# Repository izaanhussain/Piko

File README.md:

# Piko
My cute mini cute keychain with ESP32-C3 SuperMini , 0.96-inch SSD1306 OLED , TTP223 touch , six indicator LEDs and a active buzzer.
the repo has a custom KiCad PCB, Gerber files and a basic Arduino animation firmware that displays the bitmapped frames of the 712 GIFs with touch and led controls.

# Details
1) ESP32-C3 SuperMini as the controller
2) 0.96-inch, 128×64 SSD1306 I²C OLED
3) Bitmap-frame animation at a target of approximately 24 FPS
4) TTP223 touch sensor input
5) Buzzer connection
6) 6 leds & 6 resitors
7) 1 transistor
8) LiPo battery connection pads
9) Custom PCB designed in KiCad
10) KiCad source files and Gerber files included

## Required Library Setup

Open Arduino IDE
Install OLED libraries: Tools -> Manage Libraries -> search Adafruit SSD1306 -> install
fig1

Add esp32 additional board manager URL: Files -> Preferences -> add https://raw.githubusercontent.com/espressif/arduino-esp32/gh-pages/package_esp32_dev_index.json to Additional Boards Manager URLs

install esp32 board manager: Tools -> Board -> Boards Manager -> search esp32 -> install esp32 by Espressif Systems

## Components 
 refer BOM.csv

## ## Display

The project uses a:

**0.96" 128×64 SSD1306 I2C OLED**

The OLED is connected directly to the ESP32-C3.

## Pin connections

The firmware uses the I²C pins given below on the ESP32-C3 SuperMini:-

| Signal | ESP32-C3 pin |
|---|---|
| OLED SDA | GPIO8 |
| OLED SCL | GPIO9 |
| OLED power | 3V3 |
| OLED ground | GND |
| TTP223 output | GPIO3 |

## 
## Firmware

The Arduino firmware and bitmap frames are provided in `Firmware' folder

## Firmware Installation 

1. Download the raw PIKO_FIRMWARE.zip file
2. open Arduino IDE
3. open PIKO_FIRMWARE.ino
4. upload to your device

### Requirements for uploading firmware

1) Arduino IDE
2) ESP32 Arduino core
3) **Adafruit GFX Library**
4) **Adafruit SSD1306**

### Upload

1. extract Firmware/PIKO_FIRMWARE.zip
2. open the PIKO_FIRMWARE.ino file
3. ensure that all_frames.h is in the same directory as the sketch
4. install the Adafruit GFX and Adafruit SSD1306 libraries using Library Manager
5. select the correct ESP32-C3 board and serial port
6. upload the sketch and open the Serial Monitor (with baud rate 115200)

The current firmware targets 42 ms per frame (means about 24 FPS).

## PCB 

## SHEMATICS

## CREDITS 
 CREDITS TO MYSELF EVERYTHINGG OWN IDEA HEHE and THIS PROJECT WAS MADE FOR #EMBASSY YSWS BY HACKCLUB

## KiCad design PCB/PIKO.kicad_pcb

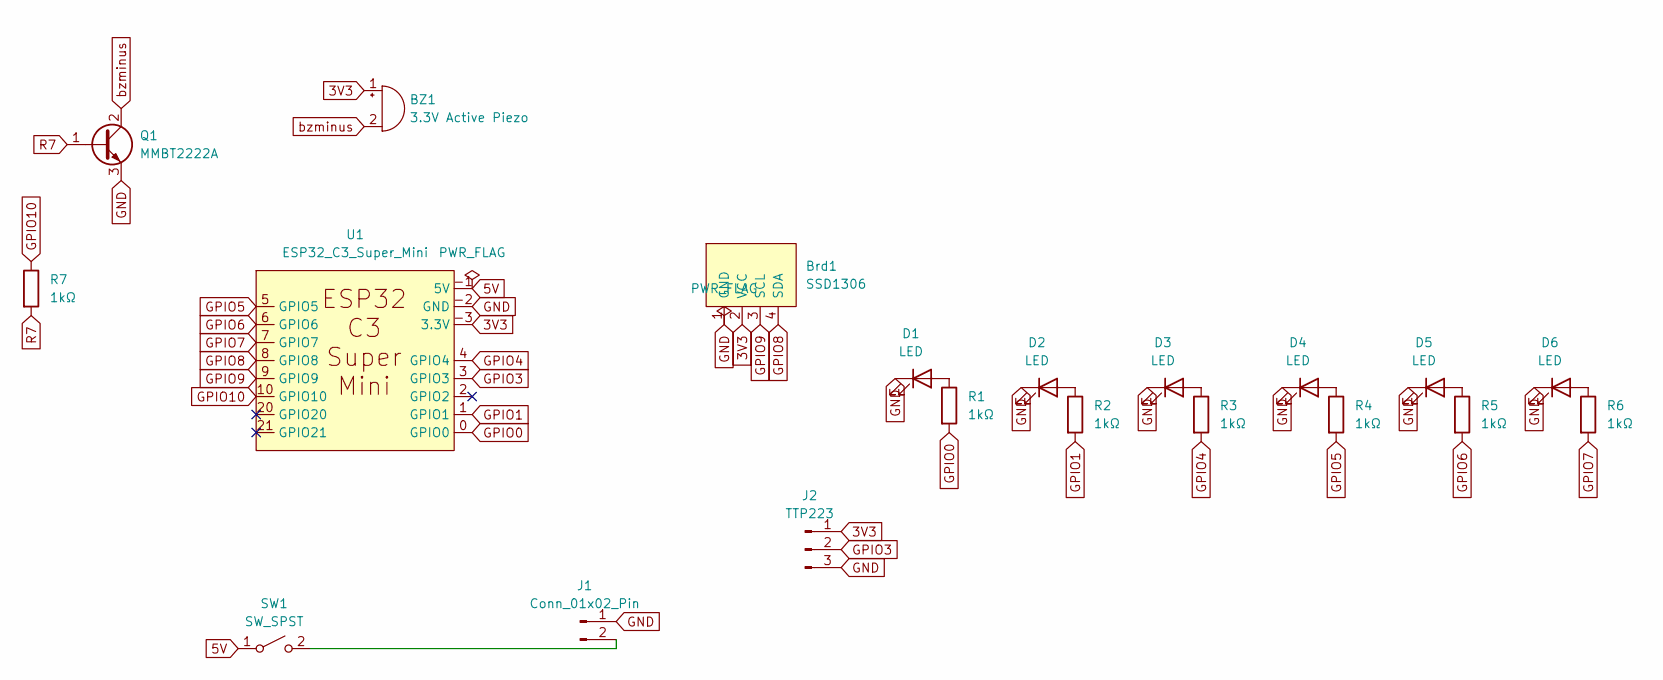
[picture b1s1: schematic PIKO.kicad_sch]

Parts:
BZ1: 3.3V Active Piezo; Buzzer_12x9.5RM7.6
Brd1: SSD1306; 128x64OLED
D1, D2, D3, D4, D5, D6: LED; LED_0603_1608Metric
J1: Conn_01x02_Pin; PinHeader_1x02_P2.54mm_Vertical
J2: TTP223; PinHeader_1x03_P2.54mm_Vertical
Q1: MMBT2222A; SOT-23
R1, R2, R3, R4, R5, R6, R7: 1kΩ; R_0603_1608Metric
SW1: SW_SPST; SW_DIP_SPSTx01_Slide_6.7x4.1mm_W8.61mm_P2.54mm_LowProfile
U1: ESP32_C3_Super_Mini

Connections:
3V3: BZ1.1 (+), Brd1.2 (VCC), J2.1, U1.-3 (3.3V)
5V: SW1.1 (A), U1.-1 (5V)
GND: Brd1.1 (GND), D1.1 (K), D2.1 (K), D3.1 (K), D4.1 (K), D5.1 (K), D6.1 (K), J1.1, J2.3, Q1.3 (E), U1.-2 (GND)
GPIO0: R1.2, U1.0 (GPIO0)
GPIO1: R2.2, U1.1 (GPIO1)
GPIO3: J2.2, U1.3 (GPIO3)
GPIO4: R3.2, U1.4 (GPIO4)
GPIO5: R4.2, U1.5 (GPIO5)
GPIO6: R5.2, U1.6 (GPIO6)
GPIO7: R6.2, U1.7 (GPIO7)
GPIO8: Brd1.4 (SDA), U1.8 (GPIO8)
GPIO9: Brd1.3 (SCL), U1.9 (GPIO9)
GPIO10: R7.1, U1.10 (GPIO10)
unnamed: D1.2 (A), R1.1
unnamed: D2.2 (A), R2.1
unnamed: D3.2 (A), R3.1
unnamed: D4.2 (A), R4.1
unnamed: D5.2 (A), R5.1
unnamed: D6.2 (A), R6.1
unnamed: J1.2, SW1.2 (B)
R7: Q1.1 (B), R7.2
bzminus: BZ1.2 (-), Q1.2 (C)

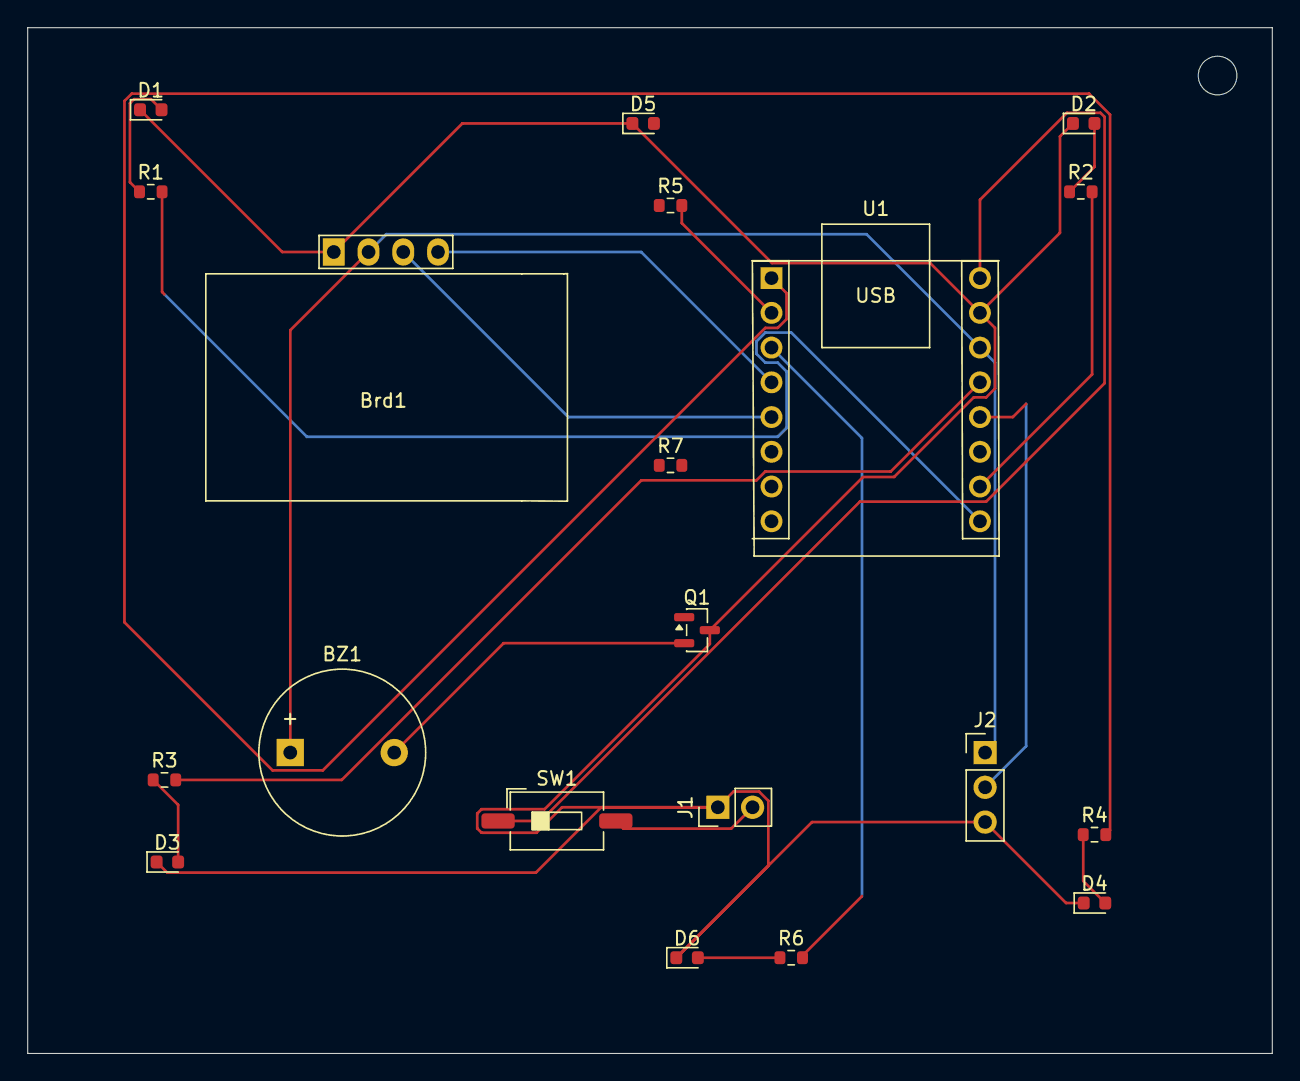
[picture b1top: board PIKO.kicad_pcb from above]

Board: 2 copper layers, 91.0 x 75.0 mm, 20 parts (0 on the bottom side), 22 nets.
